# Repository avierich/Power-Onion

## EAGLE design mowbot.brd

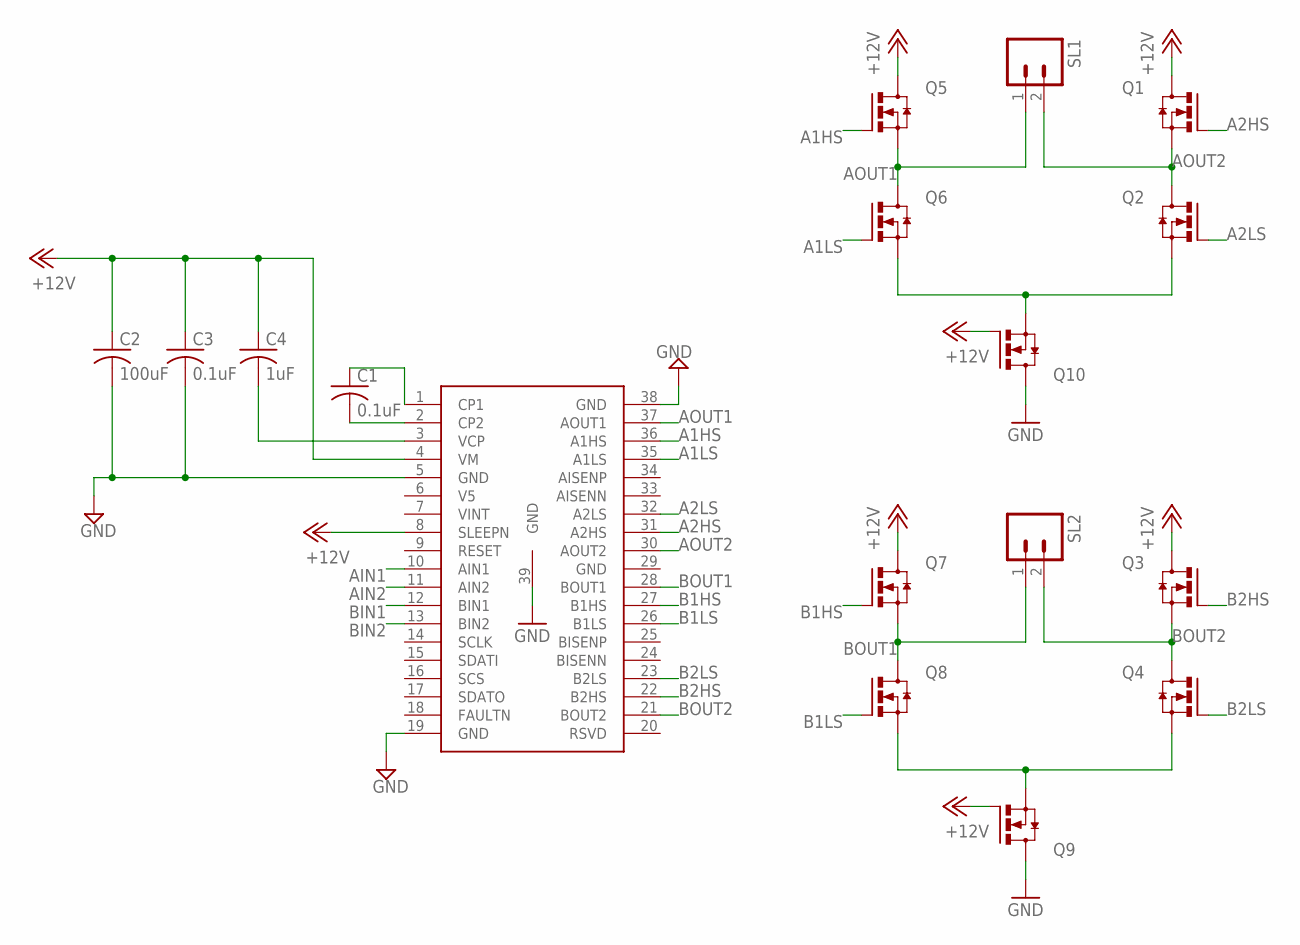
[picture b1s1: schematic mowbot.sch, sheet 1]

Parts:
C1, C3: 0.1uF; C0603
C2: 100uF; C0603
C4: 1uF; C0603
Q1, Q2, Q3, Q4, Q5, Q6, Q7, Q8, Q9, Q10: PSMN9R1-30YL-MOSFET_N; SOT669
SL1, SL2: M02; 02P
U$1: DRV8704-HBRIDGE_DRIVER; DRV8704-HBRIDGE-DRIVER

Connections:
+12V: C2.1, C3.1, C4.1, Q1.MB (D), Q3.MB (D), Q5.MB (D), Q7.MB (D), Q9.4 (G), Q10.4 (G), U$1.4 (VM), U$1.8 (SLEEPN); also elsewhere on the board
A1HS: Q5.4 (G), U$1.36 (A1HS)
A1LS: Q6.4 (G), U$1.35 (A1LS)
A2HS: Q1.4 (G), U$1.31 (A2HS)
A2LS: Q2.4 (G), U$1.32 (A2LS)
AIN1: U$1.10 (AIN1); also elsewhere on the board
AIN2: U$1.11 (AIN2); also elsewhere on the board
AOUT1: Q5.1 (S), Q5.2 (S), Q5.3 (S), Q6.MB (D), SL1.1, U$1.37 (AOUT1)
AOUT2: Q1.1 (S), Q1.2 (S), Q1.3 (S), Q2.MB (D), SL1.2, U$1.30 (AOUT2)
B1HS: Q7.4 (G), U$1.27 (B1HS)
B1LS: Q8.4 (G), U$1.26 (B1LS)
B2HS: Q3.4 (G), U$1.22 (B2HS)
B2LS: Q4.4 (G), U$1.23 (B2LS)
BIN1: U$1.12 (BIN1); also elsewhere on the board
BIN2: U$1.13 (BIN2); also elsewhere on the board
BOUT1: Q7.1 (S), Q7.2 (S), Q7.3 (S), Q8.MB (D), SL2.1, U$1.28 (BOUT1)
BOUT2: Q3.1 (S), Q3.2 (S), Q3.3 (S), Q4.MB (D), SL2.2, U$1.21 (BOUT2)
GND: C2.2, C3.2, Q9.MB (D), Q10.MB (D), U$1.5 (GND), U$1.19 (GND), U$1.38 (GND), U$1.39 (GND); also elsewhere on the board
unnamed: C1.2, U$1.2 (CP2)
unnamed: C4.2, U$1.3 (VCP)
unnamed: C1.1, U$1.1 (CP1)
unnamed: Q4.1 (S), Q4.2 (S), Q4.3 (S), Q8.1 (S), Q8.2 (S), Q8.3 (S), Q9.1 (S), Q9.2 (S), Q9.3 (S)
unnamed: Q2.1 (S), Q2.2 (S), Q2.3 (S), Q6.1 (S), Q6.2 (S), Q6.3 (S), Q10.1 (S), Q10.2 (S), Q10.3 (S)

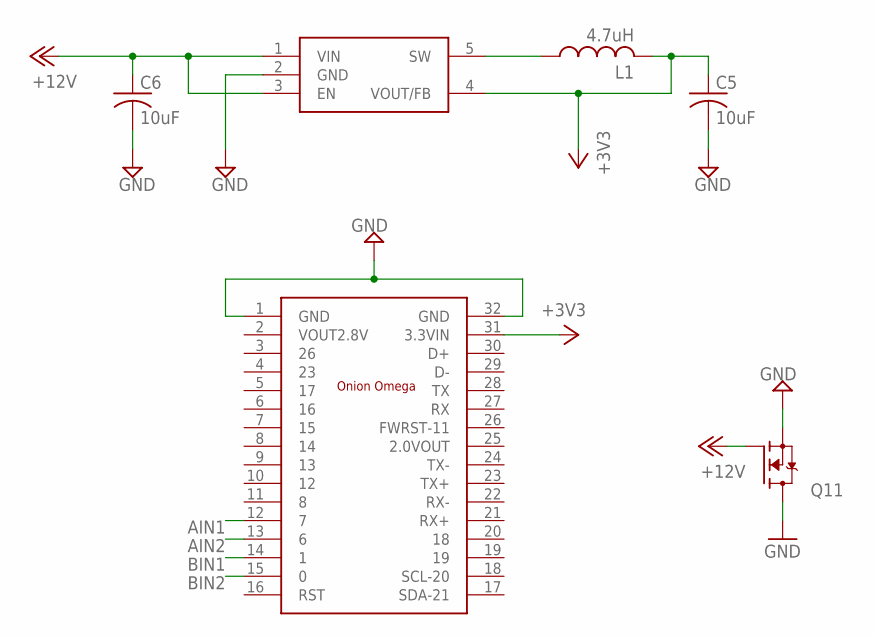
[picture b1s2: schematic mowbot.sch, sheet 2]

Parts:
C5, C6: 10uF; C0603
L1: 4.7uH; L1812
Q11: DMG2302UK-NMOSFET; SOT23
U$2: ONION_OMEGA
U$3: PAM2305; SOT23-5

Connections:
+3V3: C5.1, L1.2, U$2.31 (3.3VIN), U$3.4 (VOUT/FB)
+12V: C6.1, Q11.1 (G), U$3.1 (VIN), U$3.3 (EN); also elsewhere on the board
AIN1: U$2.12 (7); also elsewhere on the board
AIN2: U$2.13 (6); also elsewhere on the board
BIN1: U$2.14 (1); also elsewhere on the board
BIN2: U$2.15 (0); also elsewhere on the board
GND: C5.2, C6.2, Q11.2 (S), Q11.3 (D), U$2.1 (GND), U$2.32 (GND), U$3.2 (GND); also elsewhere on the board
unnamed: L1.1, U$3.5 (SW)

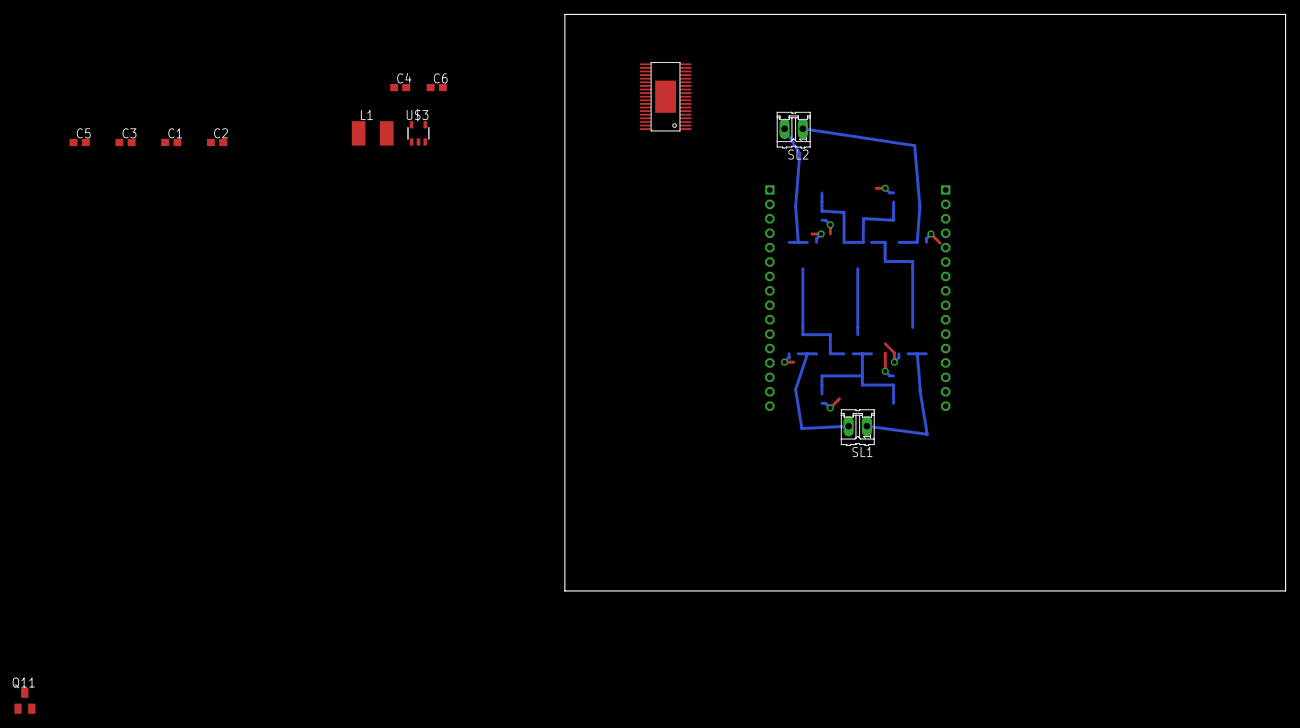
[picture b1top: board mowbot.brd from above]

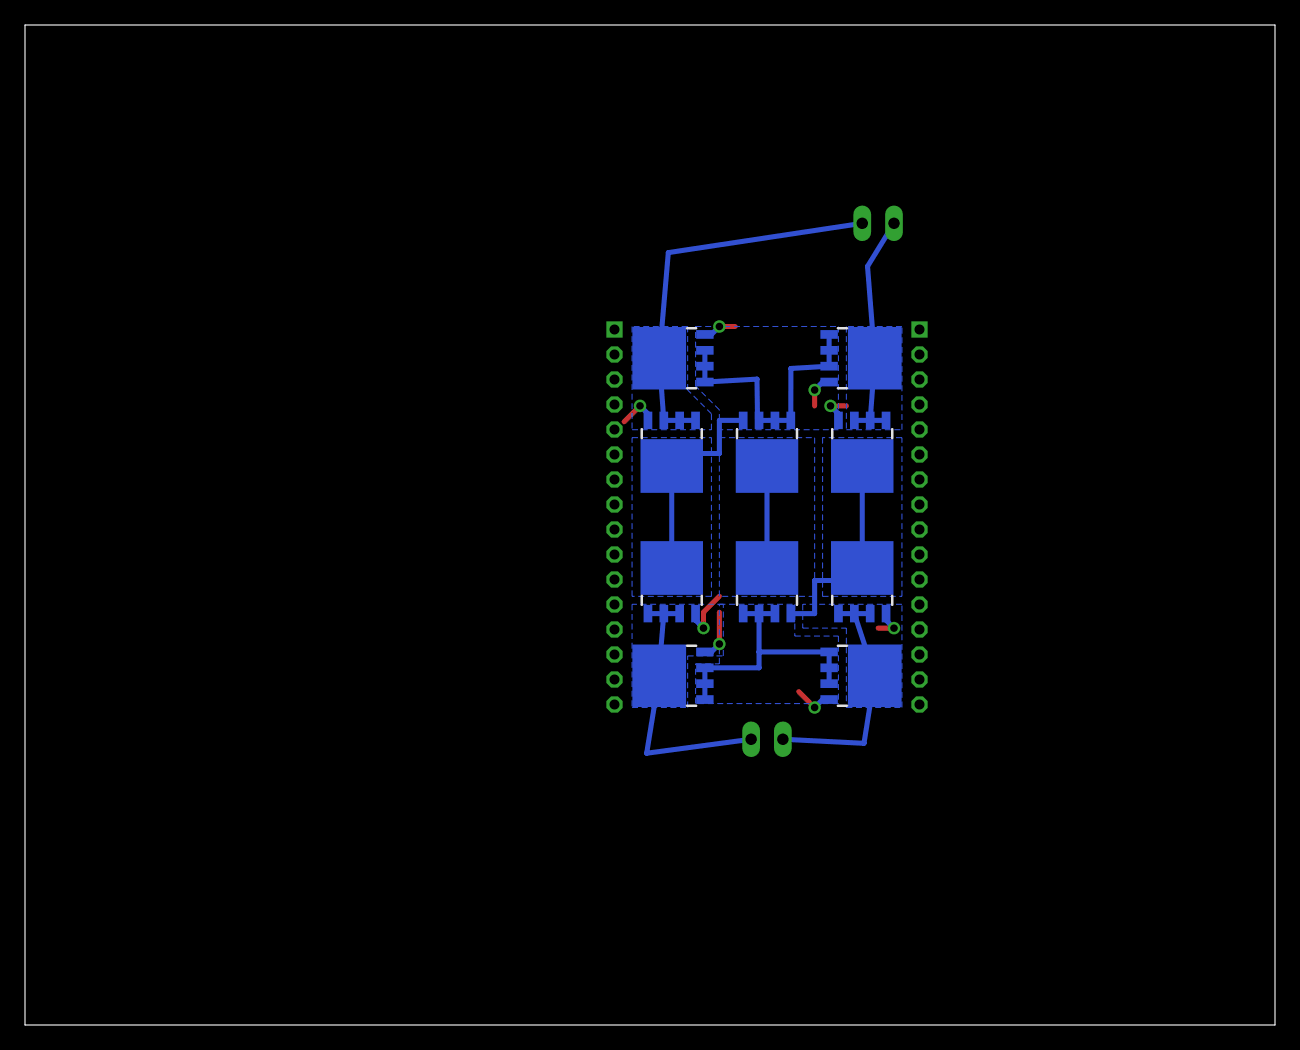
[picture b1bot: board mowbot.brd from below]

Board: 2 copper layers, 100.0 x 80.0 mm, 23 parts (10 on the bottom side), 25 nets.

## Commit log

2016-07-19 inital commit
2016-07-23 Arranged power FETs
2016-07-26 Added reverse battery protection
2016-07-26 Adding gitignore file
2016-07-29 replaced fets and routed them
